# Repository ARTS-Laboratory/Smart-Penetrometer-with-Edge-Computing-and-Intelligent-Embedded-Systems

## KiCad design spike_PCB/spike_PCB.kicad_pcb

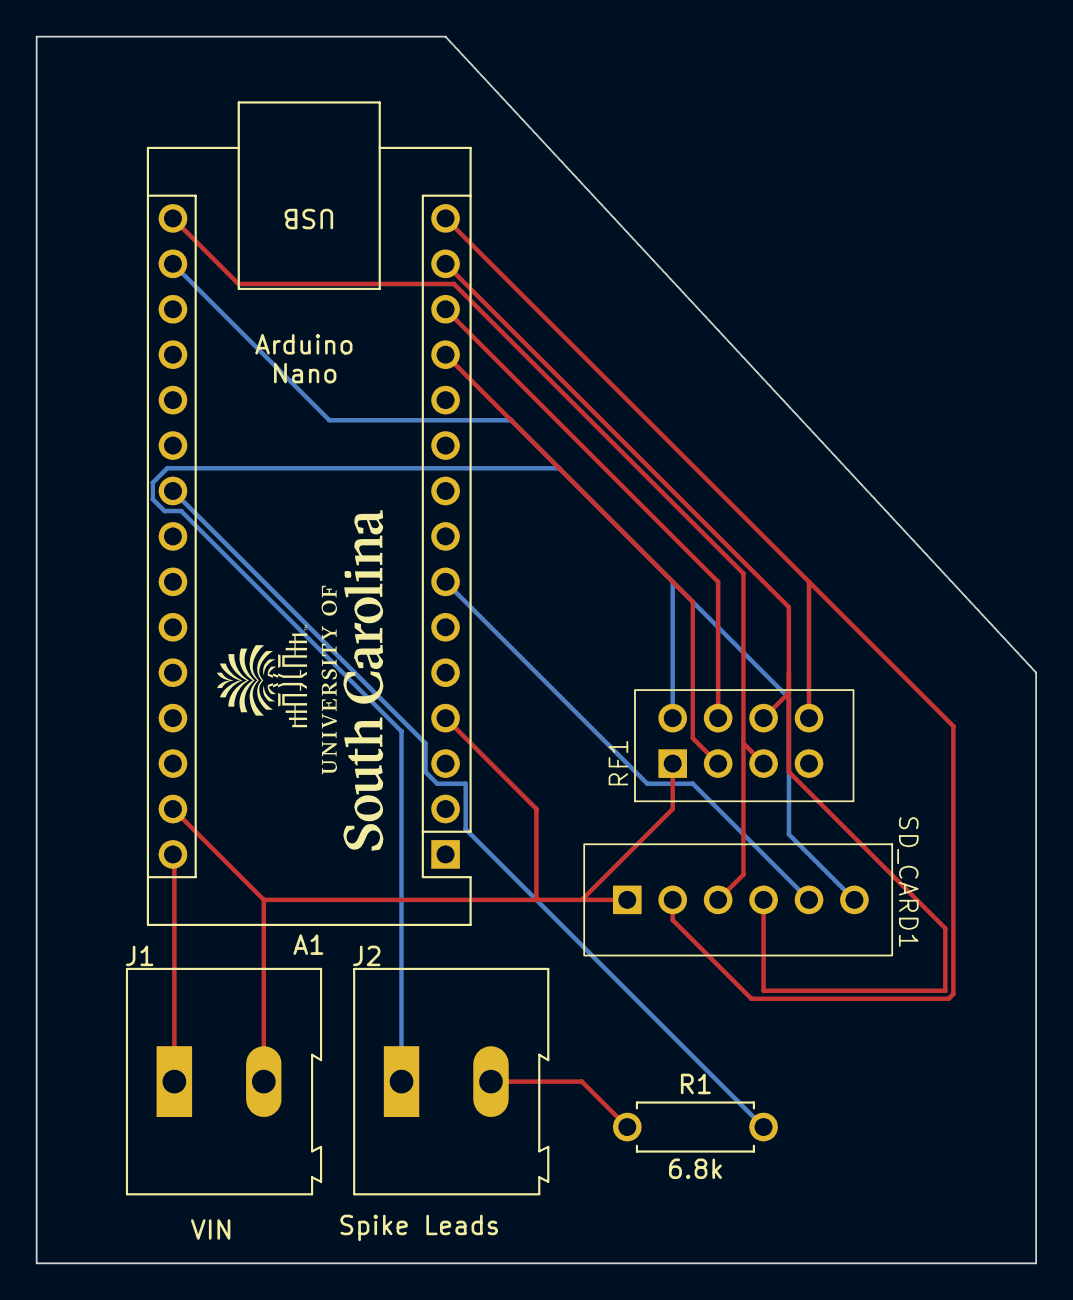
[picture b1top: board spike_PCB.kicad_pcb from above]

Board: 2 copper layers, 55.9 x 68.6 mm, 6 parts (0 on the bottom side), 11 nets.

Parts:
A1: Arduino_Nano_Every; Arduino_Nano
J1: Power_Input_Screw_Terminal; TerminalBlock_Altech_AK300-2_P5.00mm
J2: Sensing_Spike_Screw_Terminal; TerminalBlock_Altech_AK300-2_P5.00mm
R1: 6.8k; R_Axial_DIN0207_L6.3mm_D2.5mm_P7.62mm_Horizontal
RF1: nRF24L01
SD_CARD1: SD_Card_Module

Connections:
GND: A1.4 (GND), A1.29 (GND), J1.2, RF1.1 (GND), SD_CARD1.6 (GND)
unnamed: A1.17 (3V3), J2.1, RF1.5 (VCC), SD_CARD1.1 (3V3)
unnamed: A1.22 (A3), R1.2
unnamed: A1.7 (D4), SD_CARD1.2 (SD_CS)
unnamed: A1.12 (D9), RF1.2 (CE)
unnamed: A1.13 (D10), RF1.6 (CNS)
unnamed: A1.15 (MISO), RF1.8 (IRQ), SD_CARD1.5 (MISO)
unnamed: A1.14 (MOSI), RF1.7 (MOSI), SD_CARD1.3 (MOSI)
unnamed: A1.16 (SCK), RF1.3 (SCK), SD_CARD1.4 (CLK)
unnamed: A1.30 (VIN), J1.1
unnamed: J2.2, R1.1
